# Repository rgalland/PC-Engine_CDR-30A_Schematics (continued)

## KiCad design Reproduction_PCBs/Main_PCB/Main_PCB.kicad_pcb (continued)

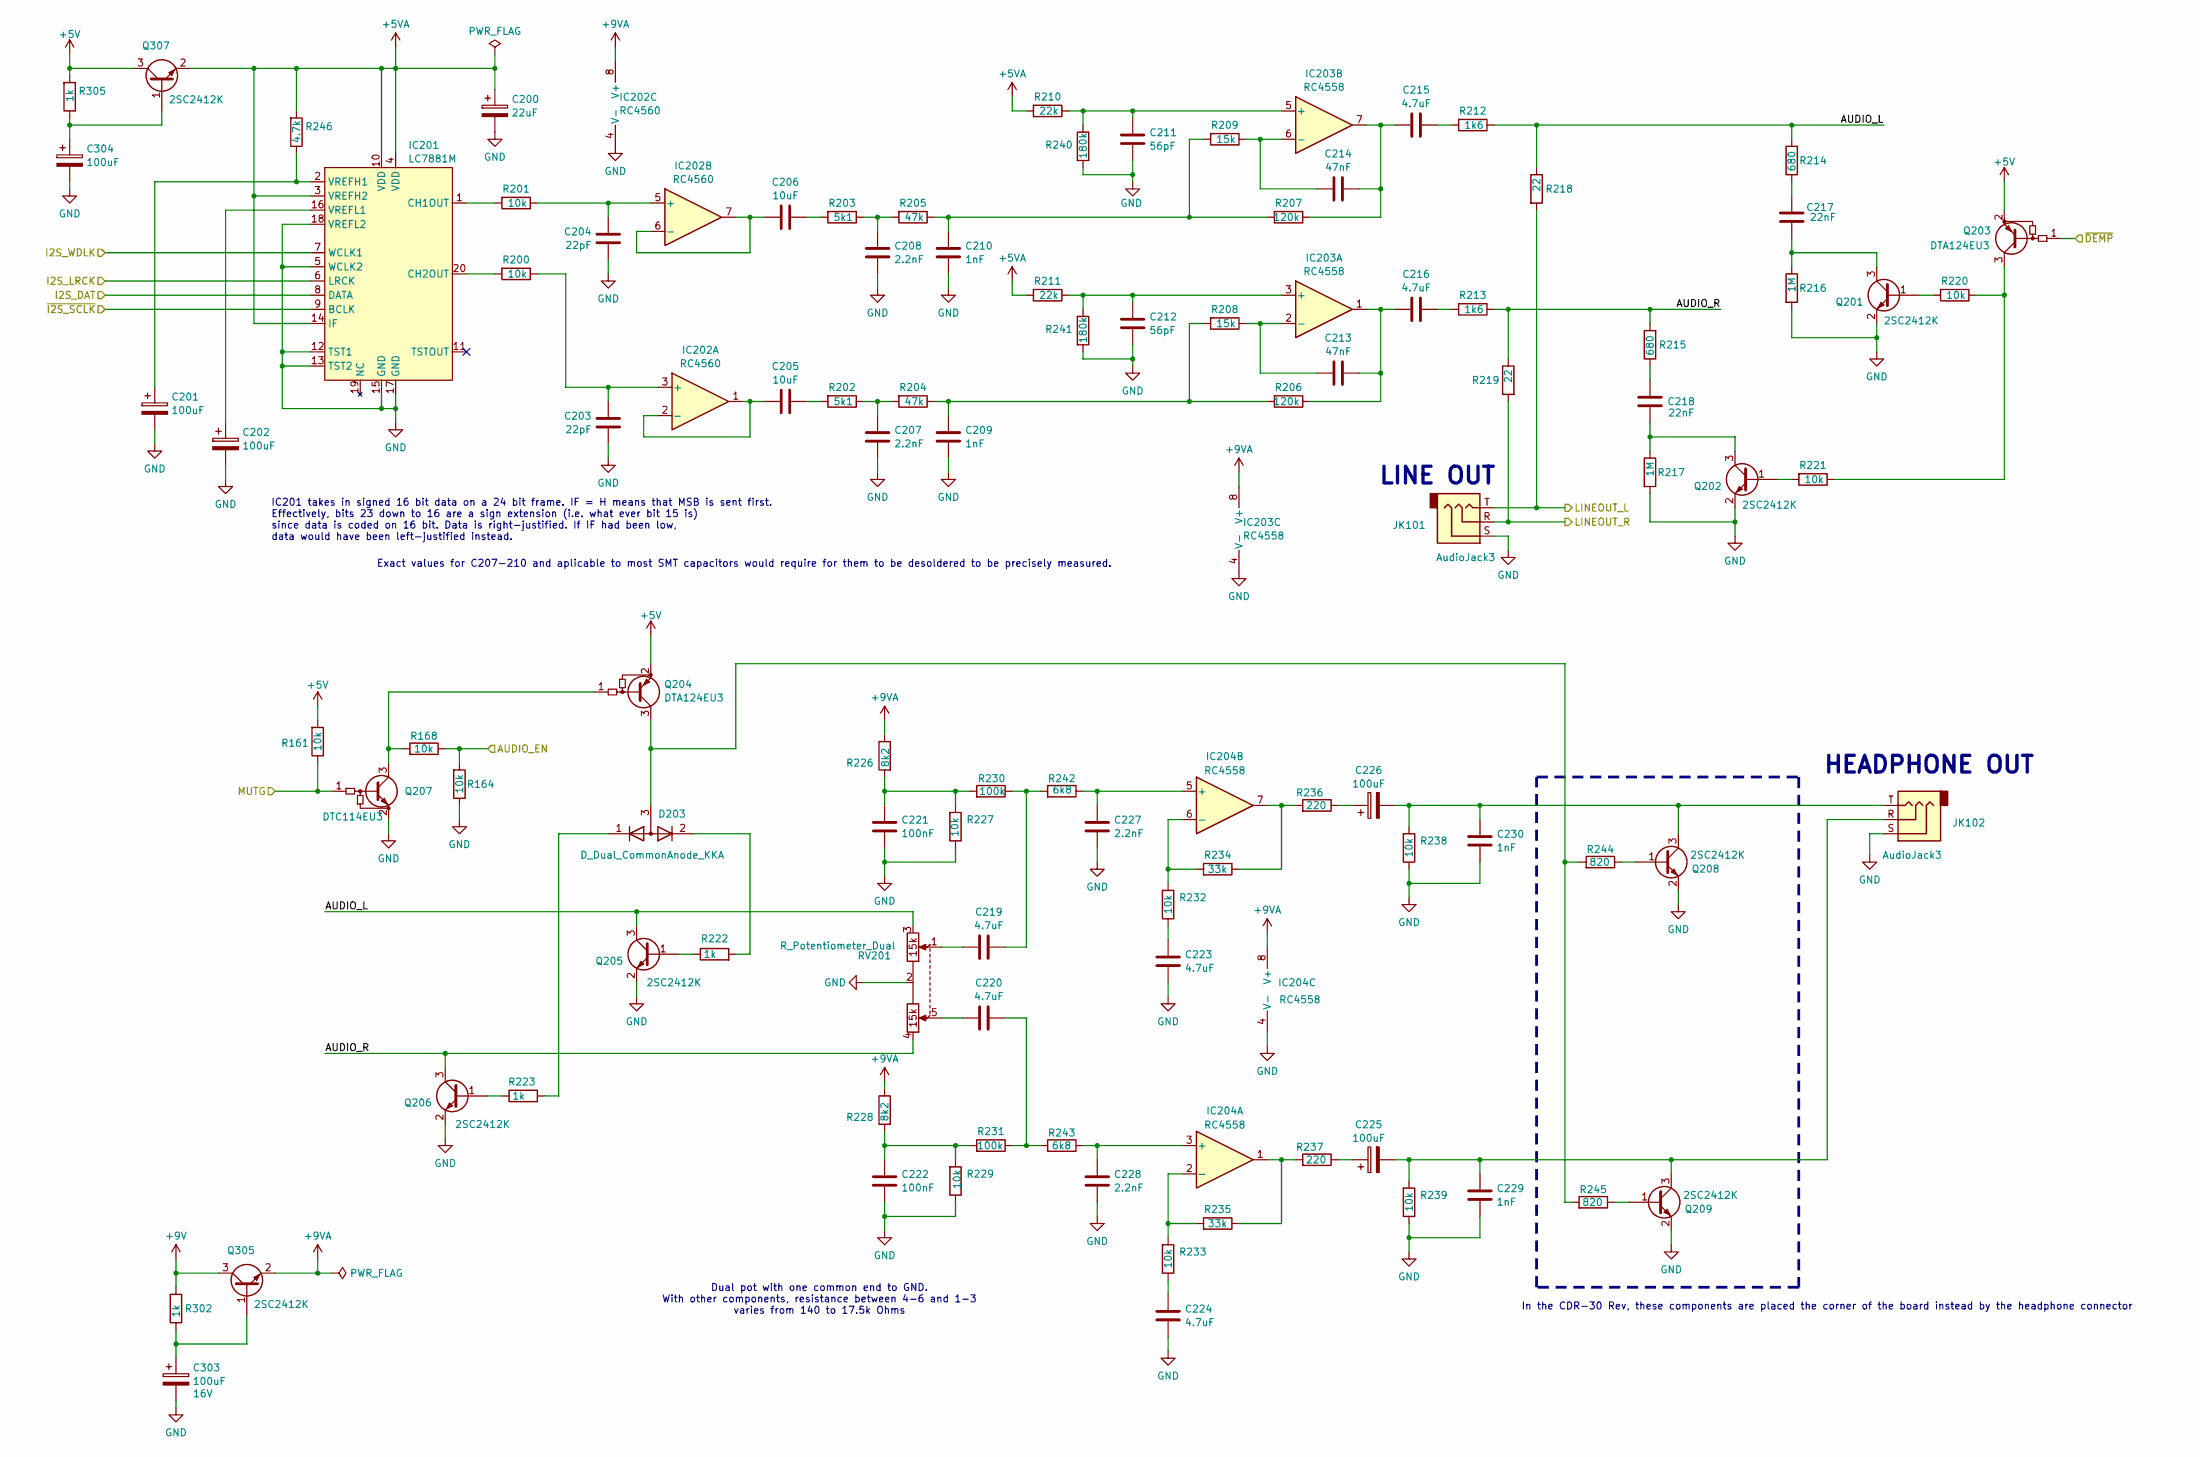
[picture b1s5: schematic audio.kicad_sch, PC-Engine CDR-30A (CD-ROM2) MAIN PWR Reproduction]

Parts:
C200: 22uF; CP_Elec_4x5.4
C201, C202, C225, C226, C304: 100uF; CP_Elec_5x5.4
C203, C204: 22pF; C_0603_1608Metric
C205, C206: 10uF; C_1206_3216Metric
C207, C208, C227, C228: 2.2nF; C_0603_1608Metric
C209, C210, C229, C230: 1nF; C_0603_1608Metric
C211, C212: 56pF; C_0603_1608Metric
C213, C214: 47nF; C_0603_1608Metric
C215, C216, C219, C220, C223, C224: 4.7uF; C_0805_2012Metric
C217, C218: 22nF; C_0603_1608Metric
C221, C222: 100nF; C_0603_1608Metric
C303: 100uF; CP_Elec_6.3x5.4; Voltage 16V
D203: D_Dual_CommonAnode_KKA; SOT-23
IC201: LC7881M; SO-20_5.3x12.6mm_P1.27mm
IC202: RC4560; SOIC-8_3.9x4.9mm_P1.27mm
IC203, IC204: RC4558; SOIC-8_3.9x4.9mm_P1.27mm
JK101, JK102: AudioJack3; Jack_3.5mm_Horizontal
Q201, Q202, Q205, Q206, Q208, Q209, Q305, Q307: 2SC2412K; SOT-23
Q203, Q204: DTA124EU3; SOT-23
Q207: DTC114EU3; SOT-23
R161, R164, R168, R200, R201, R220, R221, R227, R229, R232, R233, R238, R239: 10k; R_0603_1608Metric
R202, R203: 5k1; R_0603_1608Metric
R204, R205: 47k; R_0603_1608Metric
R206, R207: 120k; R_0603_1608Metric
R208, R209: 15k; R_0603_1608Metric
R210, R211: 22k; R_0603_1608Metric
R212, R213: 1k6; R_0603_1608Metric
R214, R215: 680; R_0603_1608Metric
R216, R217: 1M; R_0603_1608Metric
R218, R219: 22; R_0603_1608Metric
R222, R223, R302, R305: 1k; R_0603_1608Metric
R226, R228: 8k2; R_0603_1608Metric
R230, R231: 100k; R_0603_1608Metric
R234, R235: 33k; R_0603_1608Metric
R236, R237: 220; R_0603_1608Metric
R240, R241: 180k; R_0603_1608Metric
R242, R243: 6k8; R_0603_1608Metric
R244, R245: 820; R_0603_1608Metric
R246: 4.7k; R_0603_1608Metric
RV201: R_Potentiometer_Dual; Potentiometer_Double_Horizontal_Common

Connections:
+5V: Q203.2 (E), Q204.2 (E), Q307.3 (C), R161.2, R305.2; also elsewhere on the board
+5VA: C200.1, IC201.3 (VREFH2), IC201.4 (VDD), IC201.10 (VDD), IC201.14 (IF), Q307.2 (E), R210.2, R211.2, R246.2
+9V: Q305.3 (C), R302.2; also elsewhere on the board
+9VA: IC202.8 (V+), IC203.8 (V+), IC204.8 (V+), Q305.2 (E), R226.1, R228.1
/AUDIO/AUDIO_L: Q205.3 (C), R212.1, R214.2, R218.1, RV201.3
/AUDIO/AUDIO_R: Q206.3 (C), R213.1, R215.2, R219.1, RV201.4
/AUDIO/LINEOUT_L: JK101.T, R218.2; also elsewhere on the board
/AUDIO/LINEOUT_R: JK101.R, R219.2; also elsewhere on the board
/AUDIO_EN: R164.2, R168.1; also elsewhere on the board
/I2S_DAT: IC201.8 (DATA); also elsewhere on the board
/I2S_LRCK: IC201.6 (LRCK); also elsewhere on the board
/I2S_WDLK: IC201.7 (WCLK1); also elsewhere on the board
/MUTG: Q207.1 (B), R161.1; also elsewhere on the board
/~DEMP: Q203.1 (B); also elsewhere on the board
/~I2S_SCLK: IC201.9 (BCLK); also elsewhere on the board
GND: C200.2, C201.2, C202.2, C203.1, C204.1, C207.1, C208.1, C209.1, C210.1, C211.1, C212.1, C221.2, C222.2, C223.2, C224.2, C227.2, C228.2, C229.2, C230.2, C303.2, C304.2, IC201.5 (WCLK2), IC201.12 (TST1), IC201.13 (TST2), IC201.15 (GND), IC201.17 (GND), IC201.18 (VREFL2), IC202.4 (V-), IC203.4 (V-), IC204.4 (V-), JK101.S, JK102.S, Q201.2 (E), Q202.2 (E), Q205.2 (E), Q206.2 (E), Q207.2 (E), Q208.2 (E), Q209.2 (E), R164.1, R216.2, R217.2, R227.1, R229.1, R238.1, R239.1, R240.2, R241.2, RV201.2; also elsewhere on the board
unnamed: C205.1, R202.2
unnamed: C206.1, R203.2
unnamed: C207.2, R202.1, R204.2
unnamed: C208.2, R203.1, R205.2
unnamed: C209.2, R204.1, R206.2, R208.2
unnamed: C210.2, R205.1, R207.2, R209.2
unnamed: C213.1, C216.1, IC203.1, R206.1
unnamed: C214.1, C215.1, IC203.7, R207.1
unnamed: C215.2, R212.2
unnamed: C216.2, R213.2
unnamed: C217.2, R214.1
unnamed: C218.2, R215.1
unnamed: C219.1, R230.1, R242.2
unnamed: C219.2, RV201.1
unnamed: C220.1, R231.1, R243.2
unnamed: C220.2, RV201.5
unnamed: C221.1, R226.2, R227.2, R230.2
unnamed: C222.1, R228.2, R229.2, R231.2
unnamed: C223.1, R232.1
unnamed: C224.1, R233.1
unnamed: C225.1, R237.1
unnamed: C226.1, R236.1
unnamed: D203.3 (A), Q204.3 (C), R244.2, R245.2
unnamed: D203.1 (K), R223.2
unnamed: D203.2 (K), R222.2
unnamed: IC201.1 (CH1OUT), R201.2
unnamed: IC201.20 (CH2OUT), R200.2
unnamed: C201.1, IC201.2 (VREFH1), R246.1
unnamed: C202.1, IC201.16 (VREFL1)
unnamed: C203.2, IC202.3 (+), R200.1
unnamed: C205.2, IC202.1, IC202.2 (-)
unnamed: C204.2, IC202.5 (+), R201.1
unnamed: C206.2, IC202.6 (-), IC202.7
unnamed: C212.2, IC203.3 (+), R211.1, R241.1
unnamed: C213.2, IC203.2 (-), R208.1
unnamed: C211.2, IC203.5 (+), R210.1, R240.1
unnamed: C214.2, IC203.6 (-), R209.1
unnamed: IC204.1, R235.1, R237.2
unnamed: IC204.7, R234.1, R236.2
unnamed: C228.1, IC204.3 (+), R243.1
unnamed: IC204.2 (-), R233.2, R235.2
unnamed: C227.1, IC204.5 (+), R242.1
unnamed: IC204.6 (-), R232.2, R234.2
unnamed: Q201.1 (B), R220.2
unnamed: C217.1, Q201.3 (C), R216.1
unnamed: Q202.1 (B), R221.2
unnamed: C218.1, Q202.3 (C), R217.1
unnamed: Q203.3 (C), R220.1, R221.1
unnamed: Q204.1 (B), Q207.3 (C), R168.2
unnamed: Q205.1 (B), R222.1
unnamed: Q206.1 (B), R223.1
unnamed: Q208.1 (B), R244.1
unnamed: C226.2, C230.1, JK102.T, Q208.3 (C), R238.2
unnamed: Q209.1 (B), R245.1
unnamed: C225.2, C229.1, JK102.R, Q209.3 (C), R239.2
unnamed: C303.1, Q305.1 (B), R302.1
unnamed: C304.1, Q307.1 (B), R305.1

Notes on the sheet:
In the CDR-30 Rev, these components are placed the corner of the board instead by the headphone connector
IC201 takes in signed 16 bit data on a 24 bit frame. IF = H means that MSB is sent first. Effectively, bits 23 down to 16 are a sign extension (i.e. what ever bit 15 is) since data is coded on 16 bit. Data is right-justified. If IF had been low, data would have been left-justified instead.
LINE OUT
HEADPHONE OUT
Exact values for C207-210 and aplicable to most SMT capacitors would require for them to be desoldered to be precisely measured.
Dual pot with one common end to GND. With other components, resistance between 4-6 and 1-3 varies from 140 to 17.5k Ohms

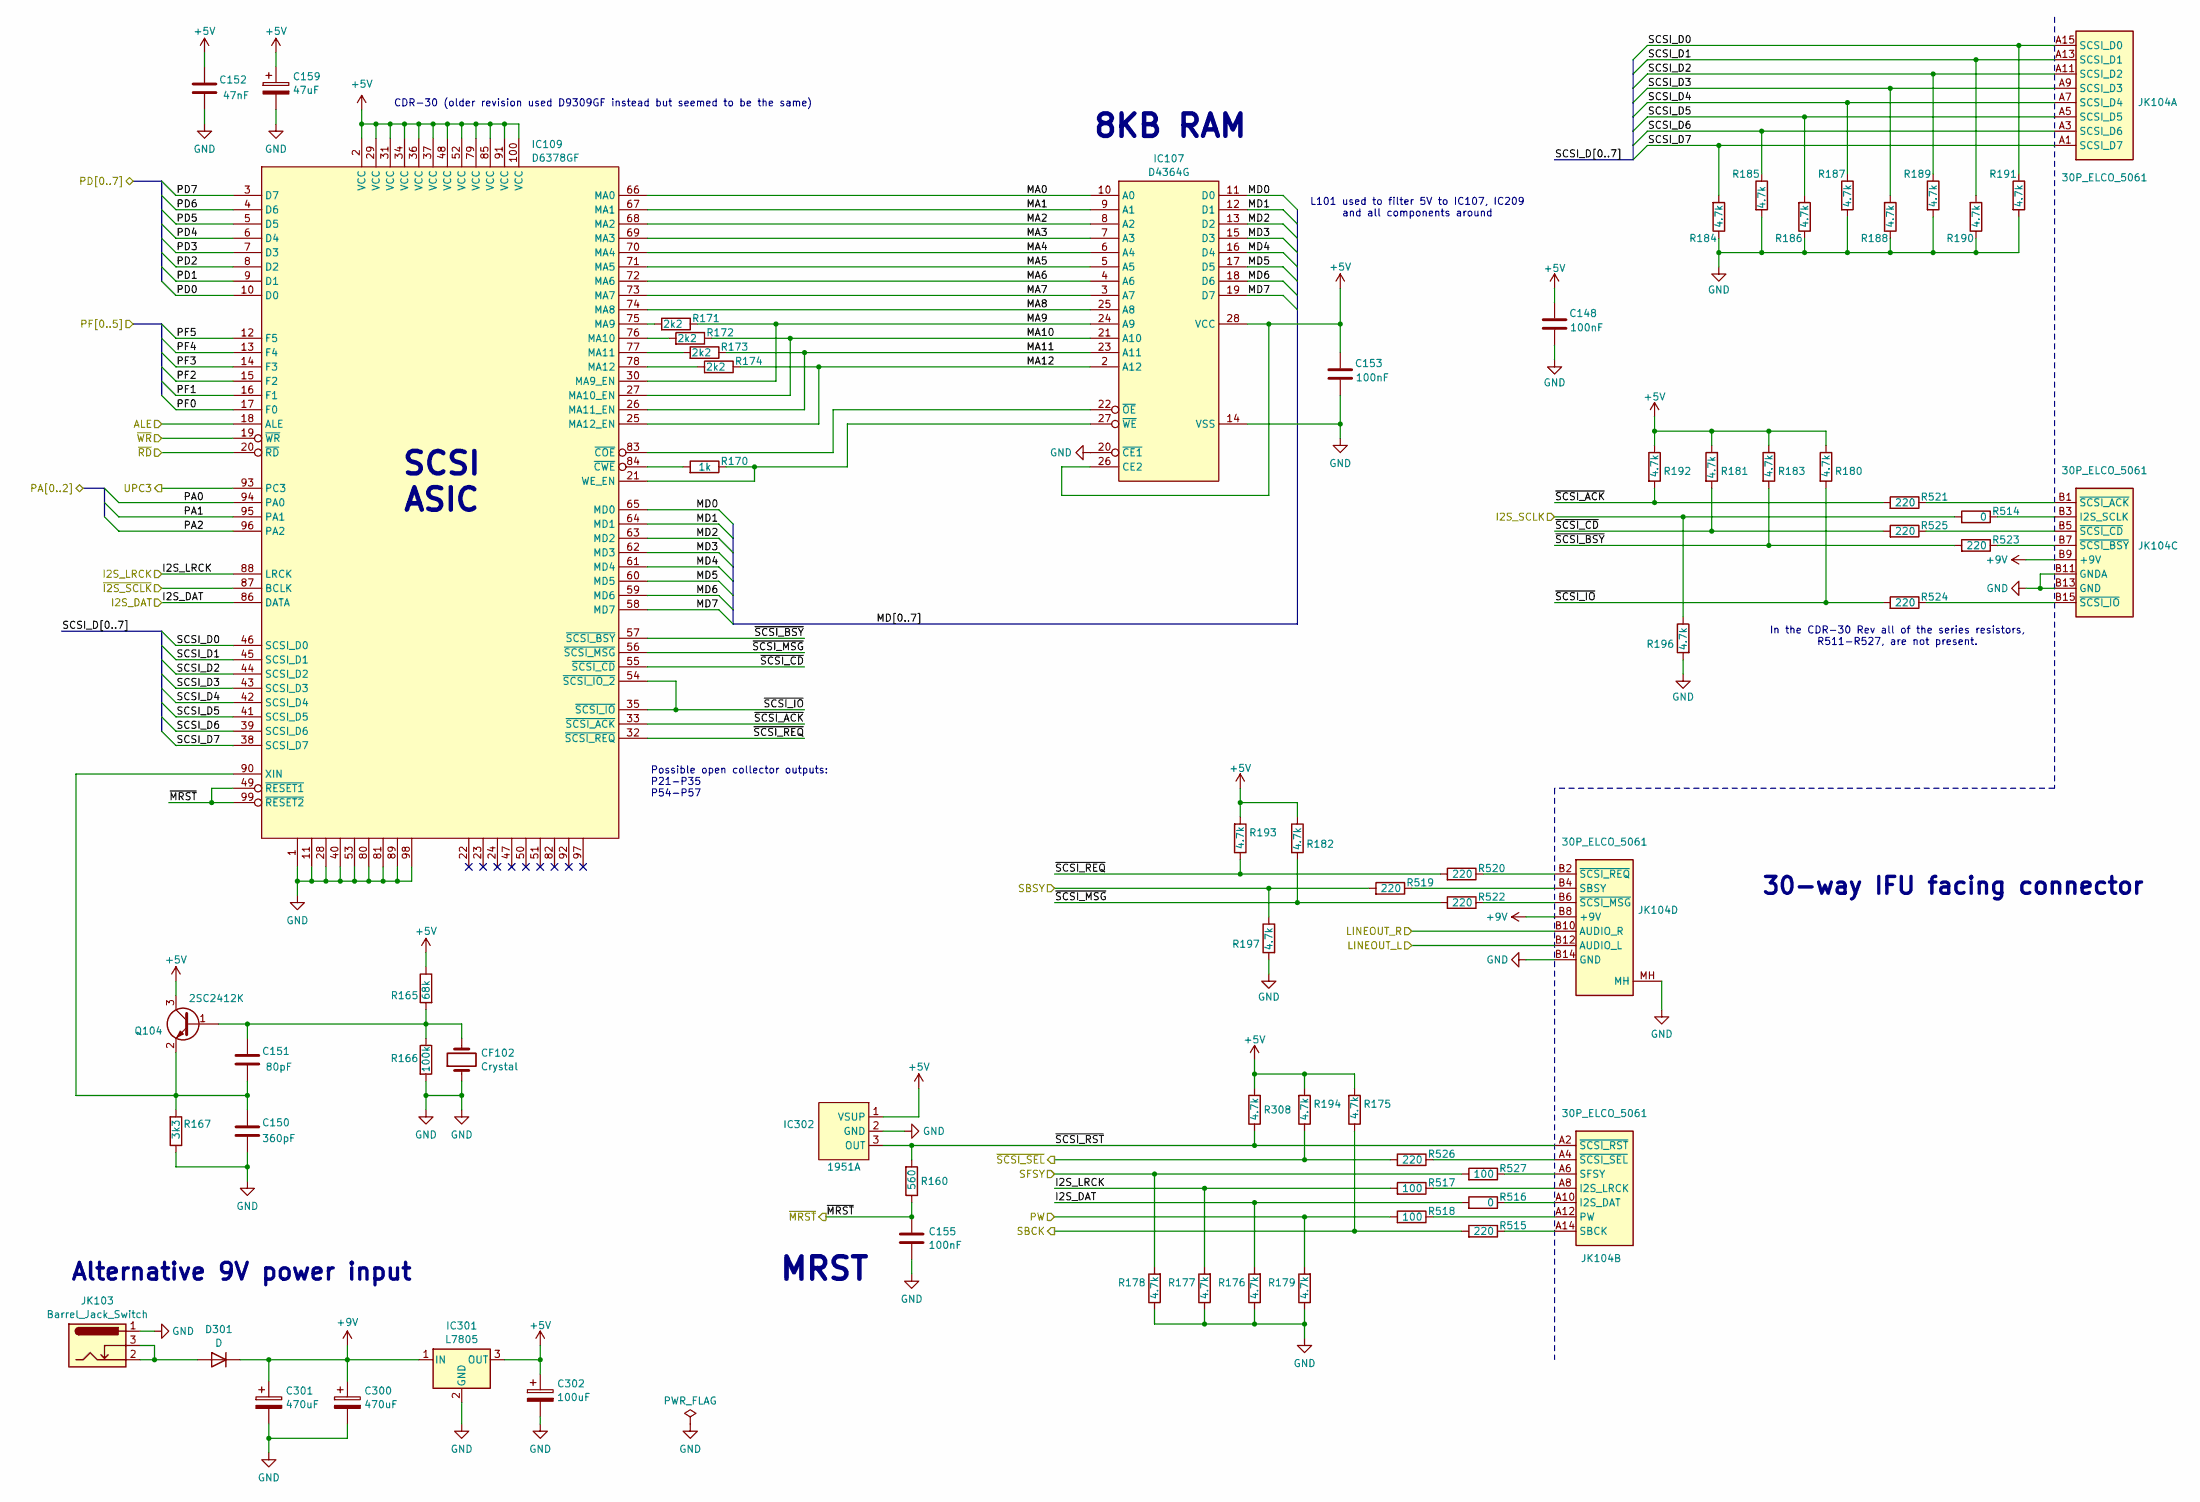
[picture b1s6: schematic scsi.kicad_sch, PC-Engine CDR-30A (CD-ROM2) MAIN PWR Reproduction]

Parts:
C148, C153, C155: 100nF; C_0603_1608Metric
C150: 360pF; C_0603_1608Metric
C151: 80pF; C_0603_1608Metric
C152: 47nF; C_0603_1608Metric
C159: 47uF; CP_Elec_5x5.4
C300, C301: 470uF; CP_Elec_8x10.5
C302: 100uF; CP_Elec_5x5.4
CF102: Crystal; Crystal_HC18-U_Vertical
D301: D; D_A-405_P10.16mm_Horizontal
IC107: D4364G; SOP-28_8.4x18.16mm_P1.27mm
IC109: D6378GF; PQFP-100_14x20mm_P0.65mm
IC301: L7805; TO-220-3_Horizontal_TabDown_HeatSink
IC302: 1951A; SOT-89-3
JK103: Barrel_Jack_Switch; BarrelJack_Horizontal
JK104: 30P_ELCO_5061; TX25-30P-LT-H1E; Manufacturer Part Number 105061030103856+
Q104: 2SC2412K; SOT-23
R160: 560; R_0603_1608Metric
R165: 68k; R_0603_1608Metric
R166: 100k; R_0603_1608Metric
R167: 3k3; R_0603_1608Metric
R170: 1k; R_0603_1608Metric
R171, R172, R173, R174: 2k2; R_0603_1608Metric
R175, R176, R177, R178, R179, R180, R181, R182, R183, R184, R185, R186, R187, R188, R189, R190, R191, R192, R193, R194, R196, R197, R308: 4.7k; R_0603_1608Metric
R514, R516: 0; R_0603_1608Metric
R515, R519, R520, R521, R522, R523, R524, R525, R526: 220; R_0603_1608Metric
R517, R518, R527: 100; R_0603_1608Metric

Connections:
+5V: C148.1, C152.2, C153.1, C159.1, C302.1, IC107.26 (CE2), IC107.28 (VCC), IC109.2 (VCC), IC109.29 (VCC), IC109.31 (VCC), IC109.34 (VCC), IC109.36 (VCC), IC109.37 (VCC), IC109.48 (VCC), IC109.52 (VCC), IC109.79 (VCC), IC109.85 (VCC), IC109.91 (VCC), IC109.100 (VCC), IC301.3 (OUT), IC302.1 (VSUP), Q104.3 (C), R165.1, R175.2, R180.1, R181.1, R182.1, R183.1, R192.1, R193.2, R194.2, R308.2; also elsewhere on the board
+9V: C300.1, C301.1, D301.1 (K), IC301.1 (IN), JK104.B8 (+9V), JK104.B9 (+9V); also elsewhere on the board
/ALE: IC109.18 (ALE); also elsewhere on the board
/AUDIO/LINEOUT_L: JK104.B12 (AUDIO_L); also elsewhere on the board
/AUDIO/LINEOUT_R: JK104.B10 (AUDIO_R); also elsewhere on the board
/I2S_DAT: IC109.86 (DATA), R176.2, R516.2; also elsewhere on the board
/I2S_LRCK: IC109.88 (LRCK), R177.2, R517.2; also elsewhere on the board
/I2S_SCLK: R196.1, R514.2; also elsewhere on the board
/PA0: IC109.94 (PA0); also elsewhere on the board
/PA1: IC109.95 (PA1); also elsewhere on the board
/PA2: IC109.96 (PA2); also elsewhere on the board
/PD0: IC109.10 (D0); also elsewhere on the board
/PD1: IC109.9 (D1); also elsewhere on the board
/PD2: IC109.8 (D2); also elsewhere on the board
/PD3: IC109.7 (D3); also elsewhere on the board
/PD4: IC109.6 (D4); also elsewhere on the board
/PD5: IC109.5 (D5); also elsewhere on the board
/PD6: IC109.4 (D6); also elsewhere on the board
/PD7: IC109.3 (D7); also elsewhere on the board
/PF0: IC109.17 (F0); also elsewhere on the board
/PF1: IC109.16 (F1); also elsewhere on the board
/PF2: IC109.15 (F2); also elsewhere on the board
/PF3: IC109.14 (F3); also elsewhere on the board
/PF4: IC109.13 (F4); also elsewhere on the board
/PF5: IC109.12 (F5); also elsewhere on the board
/PW: R179.2, R518.2; also elsewhere on the board
/SBCK: R175.1, R515.2; also elsewhere on the board
/SBSY: R197.1, R519.2; also elsewhere on the board
/SCSI/MA0: IC107.10 (A0), IC109.66 (MA0)
/SCSI/MA1: IC107.9 (A1), IC109.67 (MA1)
/SCSI/MA2: IC107.8 (A2), IC109.68 (MA2)
/SCSI/MA3: IC107.7 (A3), IC109.69 (MA3)
/SCSI/MA4: IC107.6 (A4), IC109.70 (MA4)
/SCSI/MA5: IC107.5 (A5), IC109.71 (MA5)
/SCSI/MA6: IC107.4 (A6), IC109.72 (MA6)
/SCSI/MA7: IC107.3 (A7), IC109.73 (MA7)
/SCSI/MA8: IC107.25 (A8), IC109.74 (MA8)
/SCSI/MA9: IC107.24 (A9), IC109.30 (MA9_EN), R171.1
/SCSI/MA10: IC107.21 (A10), IC109.27 (MA10_EN), R172.1
/SCSI/MA11: IC107.23 (A11), IC109.26 (MA11_EN), R173.1
/SCSI/MA12: IC107.2 (A12), IC109.25 (MA12_EN), R174.1
/SCSI/MD0: IC107.11 (D0), IC109.65 (MD0)
/SCSI/MD1: IC107.12 (D1), IC109.64 (MD1)
/SCSI/MD2: IC107.13 (D2), IC109.63 (MD2)
/SCSI/MD3: IC107.15 (D3), IC109.62 (MD3)
/SCSI/MD4: IC107.16 (D4), IC109.61 (MD4)
/SCSI/MD5: IC107.17 (D5), IC109.60 (MD5)
/SCSI/MD6: IC107.18 (D6), IC109.59 (MD6)
/SCSI/MD7: IC107.19 (D7), IC109.58 (MD7)
/SCSI/SCSI_D0: IC109.46 (SCSI_D0), JK104.A15 (SCSI_D0), R191.1
/SCSI/SCSI_D1: IC109.45 (SCSI_D1), JK104.A13 (SCSI_D1), R190.2
/SCSI/SCSI_D2: IC109.44 (SCSI_D2), JK104.A11 (SCSI_D2), R189.1
/SCSI/SCSI_D3: IC109.43 (SCSI_D3), JK104.A9 (SCSI_D3), R188.2
/SCSI/SCSI_D4: IC109.42 (SCSI_D4), JK104.A7 (SCSI_D4), R187.1
/SCSI/SCSI_D5: IC109.41 (SCSI_D5), JK104.A5 (SCSI_D5), R186.2
/SCSI/SCSI_D6: IC109.39 (SCSI_D6), JK104.A3 (SCSI_D6), R185.1
/SCSI/SCSI_D7: IC109.38 (SCSI_D7), JK104.A1 (SCSI_D7), R184.2
/SCSI/~SCSI_ACK: IC109.33 (~SCSI_ACK), R192.2, R521.2
/SCSI/~SCSI_BSY: IC109.57 (~SCSI_BSY), R183.2, R523.2
/SCSI/~SCSI_CD: IC109.55 (~SCSI_CD), R181.2, R525.2
/SCSI/~SCSI_IO: IC109.35 (~SCSI_IO), IC109.54 (~SCSI_IO_2), R180.2, R524.2
/SCSI/~SCSI_MSG: IC109.56 (~SCSI_MSG), R182.2, R522.2
/SCSI/~SCSI_REQ: IC109.32 (~SCSI_REQ), R193.1, R520.2
/SCSI/~SCSI_RST: IC302.3 (OUT), JK104.A2 (~SCSI_RST), R160.2, R308.1
/SFSY: R178.2, R527.2; also elsewhere on the board
/UPC3: IC109.93 (PC3); also elsewhere on the board
/~I2S_SCLK: IC109.87 (BCLK); also elsewhere on the board
/~MRST: C155.1, IC109.49 (~RESET1), IC109.99 (~RESET2), R160.1; also elsewhere on the board
/~RD: IC109.20 (~RD); also elsewhere on the board
/~SCSI_SEL: R194.1, R526.2; also elsewhere on the board
/~WR: IC109.19 (~WR); also elsewhere on the board
GND: C148.2, C150.1, C152.1, C153.2, C155.2, C159.2, C300.2, C301.2, C302.2, CF102.1, IC107.14 (VSS), IC107.20 (~CE1), IC109.1, IC109.11, IC109.28, IC109.40, IC109.53, IC109.80, IC109.81, IC109.89, IC109.98, IC301.2 (GND), IC302.2 (GND), JK103.1, JK104.B11 (GNDA), JK104.B13 (GND), JK104.B14 (GND), JK104.MH, R166.2, R167.1, R176.1, R177.1, R178.1, R179.1, R184.1, R185.2, R186.1, R187.2, R188.1, R189.2, R190.1, R191.2, R196.2, R197.2; also elsewhere on the board
unnamed: D301.2 (A), JK103.2, JK103.3
unnamed: IC107.22 (~OE), IC109.83 (~COE)
unnamed: IC107.27 (~WE), IC109.21 (WE_EN), R170.1
unnamed: IC109.75 (MA9), R171.2
unnamed: IC109.76 (MA10), R172.2
unnamed: IC109.77 (MA11), R173.2
unnamed: IC109.78 (MA12), R174.2
unnamed: C150.2, C151.1, IC109.90 (XIN), Q104.2 (E), R167.2
unnamed: IC109.84 (~CWE), R170.2
unnamed: JK104.A10 (I2S_DAT), R516.1
unnamed: JK104.A8 (I2S_LRCK), R517.1
unnamed: JK104.A12 (PW), R518.1
unnamed: JK104.A14 (SBCK), R515.1
unnamed: JK104.A6 (SFSY), R527.1
unnamed: JK104.A4 (~SCSI_SEL), R526.1
unnamed: JK104.B3 (I2S_SCLK), R514.1
unnamed: JK104.B1 (~SCSI_ACK), R521.1
unnamed: JK104.B7 (~SCSI_BSY), R523.1
unnamed: JK104.B5 (~SCSI_CD), R525.1
unnamed: JK104.B15 (~SCSI_IO), R524.1
unnamed: JK104.B4 (SBSY), R519.1
unnamed: JK104.B6 (~SCSI_MSG), R522.1
unnamed: JK104.B2 (~SCSI_REQ), R520.1
unnamed: C151.2, CF102.2, Q104.1 (B), R165.2, R166.1

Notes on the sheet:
MRST
30-way IFU facing connector
L101 used to filter 5V to IC107, IC209 and all components around
8KB RAM
Possible open collector outputs: P21-P35 P54-P57
SCSI ASIC
In the CDR-30 Rev all of the series resistors, R511-R527, are not present.
Alternative 9V power input
CDR-30 (older revision used D9309GF instead but seemed to be the same)

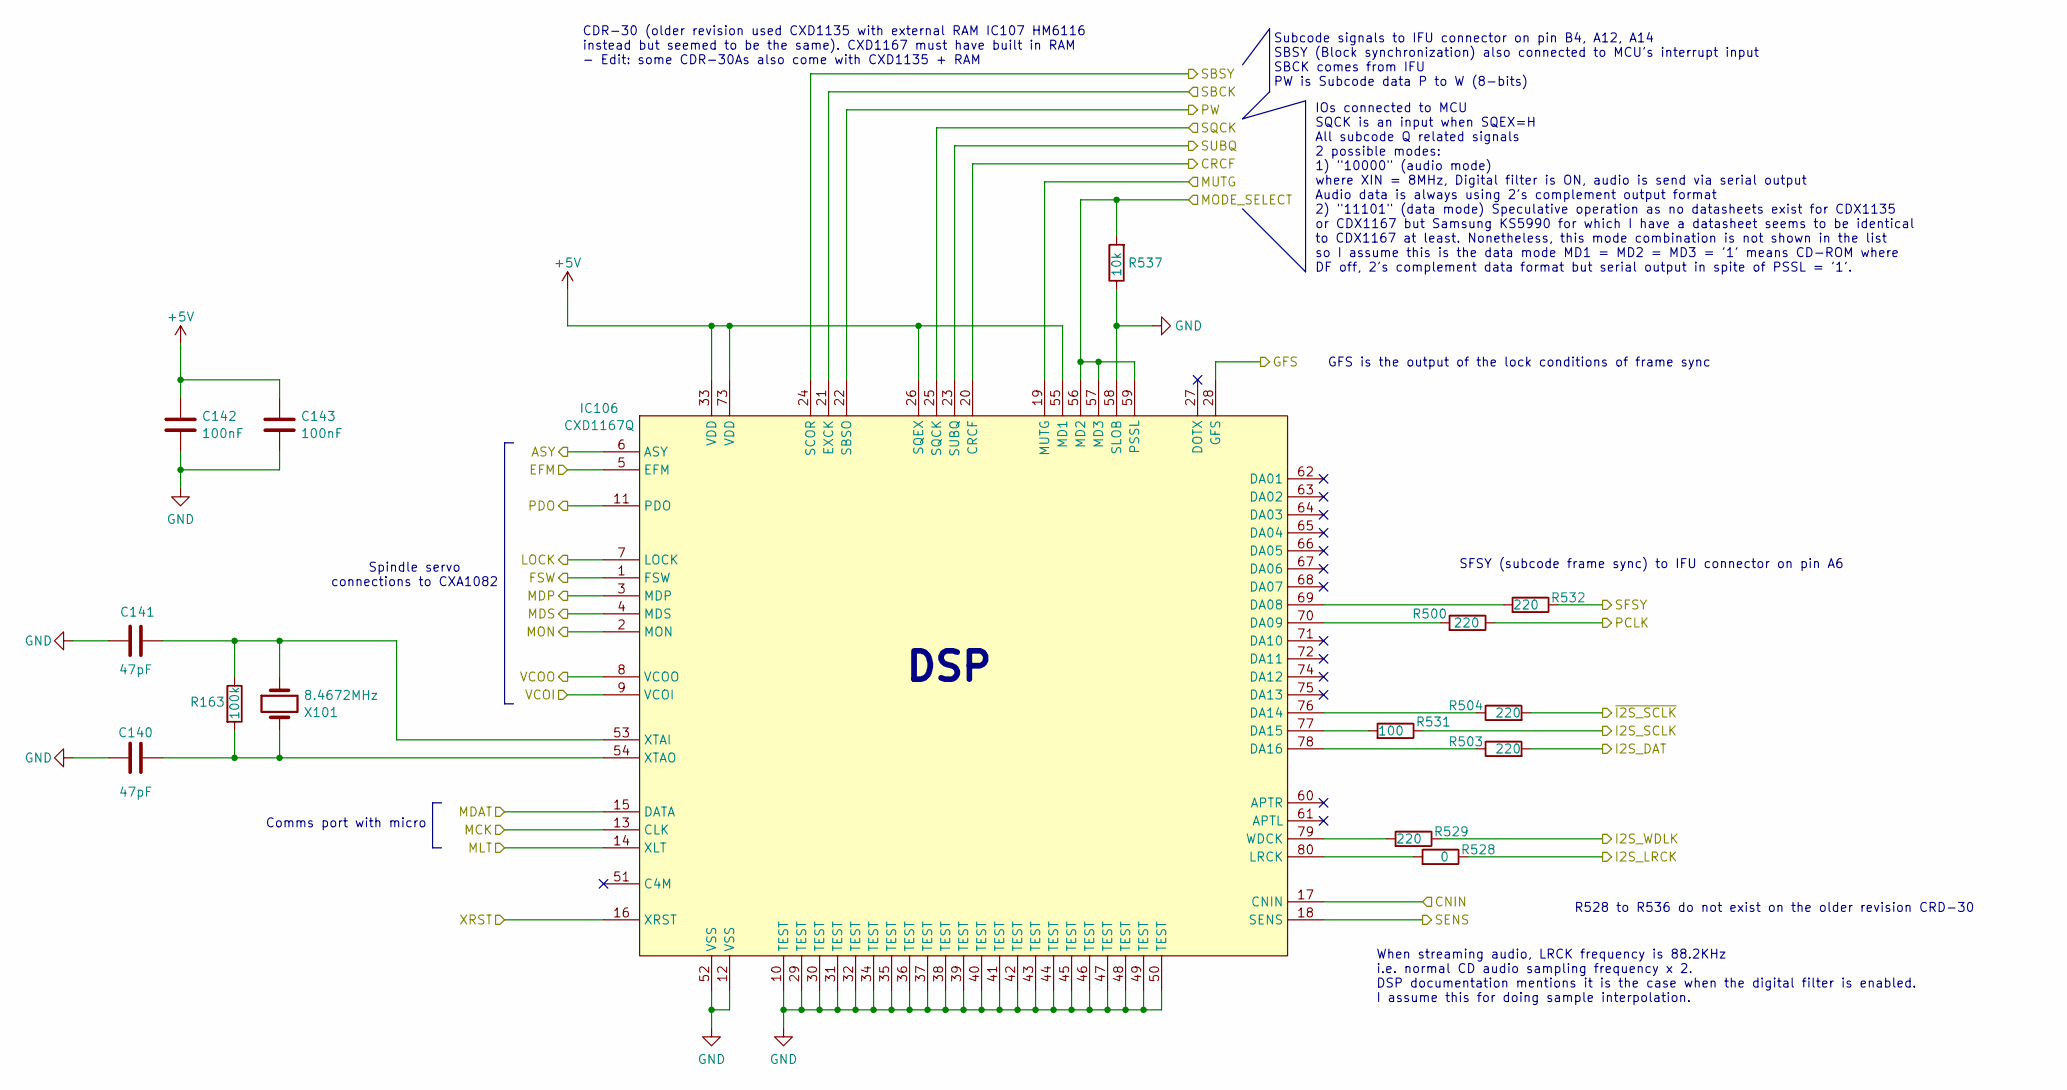
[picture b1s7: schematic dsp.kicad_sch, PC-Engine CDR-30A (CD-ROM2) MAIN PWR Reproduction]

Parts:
C140, C141: 47pF; C_0603_1608Metric
C142, C143: 100nF; C_0603_1608Metric
IC106: CXD1167Q; PQFP-80_14x20mm_P0.8mm
R163: 100k; R_0603_1608Metric
R500, R503, R504, R529, R532: 220; R_0603_1608Metric
R528: 0; R_0603_1608Metric
R531: 100; R_0603_1608Metric
R537: 10k; R_0603_1608Metric
X101: 8.4672MHz; Crystal_HC18-U_Horizontal

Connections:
+5V: C142.1, C143.1, IC106.26 (SQEX), IC106.33 (VDD), IC106.55 (MD1), IC106.73 (VDD); also elsewhere on the board
/CNIN: IC106.17 (CNIN); also elsewhere on the board
/CRCF: IC106.20 (CRCF); also elsewhere on the board
/DSP/ASY: IC106.6 (ASY); also elsewhere on the board
/DSP/EFM: IC106.5 (EFM); also elsewhere on the board
/DSP/PCLK: R500.1; also elsewhere on the board
/FSW: IC106.1 (FSW); also elsewhere on the board
/GFS: IC106.28 (GFS); also elsewhere on the board
/I2S_DAT: R503.2; also elsewhere on the board
/I2S_LRCK: R528.1; also elsewhere on the board
/I2S_SCLK: R531.1; also elsewhere on the board
/I2S_WDLK: R529.1; also elsewhere on the board
/LOCK: IC106.7 (LOCK); also elsewhere on the board
/MCK: IC106.13 (CLK); also elsewhere on the board
/MDAT: IC106.15 (DATA); also elsewhere on the board
/MDP: IC106.3 (MDP); also elsewhere on the board
/MDS: IC106.4 (MDS); also elsewhere on the board
/MLT: IC106.14 (XLT); also elsewhere on the board
/MODE_SELECT: IC106.56 (MD2), IC106.57 (MD3), IC106.59 (PSSL), R537.2; also elsewhere on the board
/MON: IC106.2 (MON); also elsewhere on the board
/MUTG: IC106.19 (MUTG); also elsewhere on the board
/PDO: IC106.11 (PDO); also elsewhere on the board
/PW: IC106.22 (SBSO); also elsewhere on the board
/SBCK: IC106.21 (EXCK); also elsewhere on the board
/SBSY: IC106.24 (SCOR); also elsewhere on the board
/SENS: IC106.18 (SENS); also elsewhere on the board
/SFSY: R532.1; also elsewhere on the board
/SQCK: IC106.25 (SQCK); also elsewhere on the board
/SUBQ: IC106.23 (SUBQ); also elsewhere on the board
/VCOI: IC106.9 (VCOI); also elsewhere on the board
/VCOO: IC106.8 (VCOO); also elsewhere on the board
/XRST: IC106.16 (XRST); also elsewhere on the board
/~I2S_SCLK: R504.2; also elsewhere on the board
GND: C140.1, C141.2, C142.2, C143.2, IC106.10 (TEST), IC106.12 (VSS), IC106.29 (TEST), IC106.30 (TEST), IC106.31 (TEST), IC106.32 (TEST), IC106.34 (TEST), IC106.35 (TEST), IC106.36 (TEST), IC106.37 (TEST), IC106.38 (TEST), IC106.39 (TEST), IC106.40 (TEST), IC106.41 (TEST), IC106.42 (TEST), IC106.43 (TEST), IC106.44 (TEST), IC106.45 (TEST), IC106.46 (TEST), IC106.47 (TEST), IC106.48 (TEST), IC106.49 (TEST), IC106.50 (TEST), IC106.52 (VSS), IC106.58 (SLOB), R537.1; also elsewhere on the board
unnamed: IC106.69 (DA08), R532.2
unnamed: IC106.70 (DA09), R500.2
unnamed: IC106.76 (DA14), R504.1
unnamed: IC106.77 (DA15), R531.2
unnamed: IC106.78 (DA16), R503.1
unnamed: IC106.80 (LRCK), R528.2
unnamed: IC106.79 (WDCK), R529.2
unnamed: C141.1, IC106.53 (XTAI), R163.1, X101.1
unnamed: C140.2, IC106.54 (XTAO), R163.2, X101.2

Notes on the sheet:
DSP
Comms port with micro
When streaming audio, LRCK frequency is 88.2KHz i.e. normal CD audio sampling frequency x 2. DSP documentation mentions it is the case when the digital filter is enabled. I assume this for doing sample interpolation.
GFS is the output of the lock conditions of frame sync
Subcode signals to IFU connector on pin B4, A12, A14 SBSY (Block synchronization) also connected to MCU's interrupt input SBCK comes from IFU PW is Subcode data P to W (8-bits)
R528 to R536 do not exist on the older revision CRD-30
IOs connected to MCU SQCK is an input when SQEX=H All subcode Q related signals 2 possible modes: 1) "10000" (audio mode) where XIN = 8MHz, Digital filter is ON, audio is send via serial output Audio data is always using 2's complement output format 2) "11101" (data mode) Speculative operation as n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
CDR-30 (older revision used CXD1135 with external RAM IC107 HM6116 instead but seemed to be the same). CXD1167 must have built in RAM - Edit: some CDR-30As also come with CXD1135 + RAM
Spindle servo connections to CXA1082
SFSY (subcode frame sync) to IFU connector on pin A6

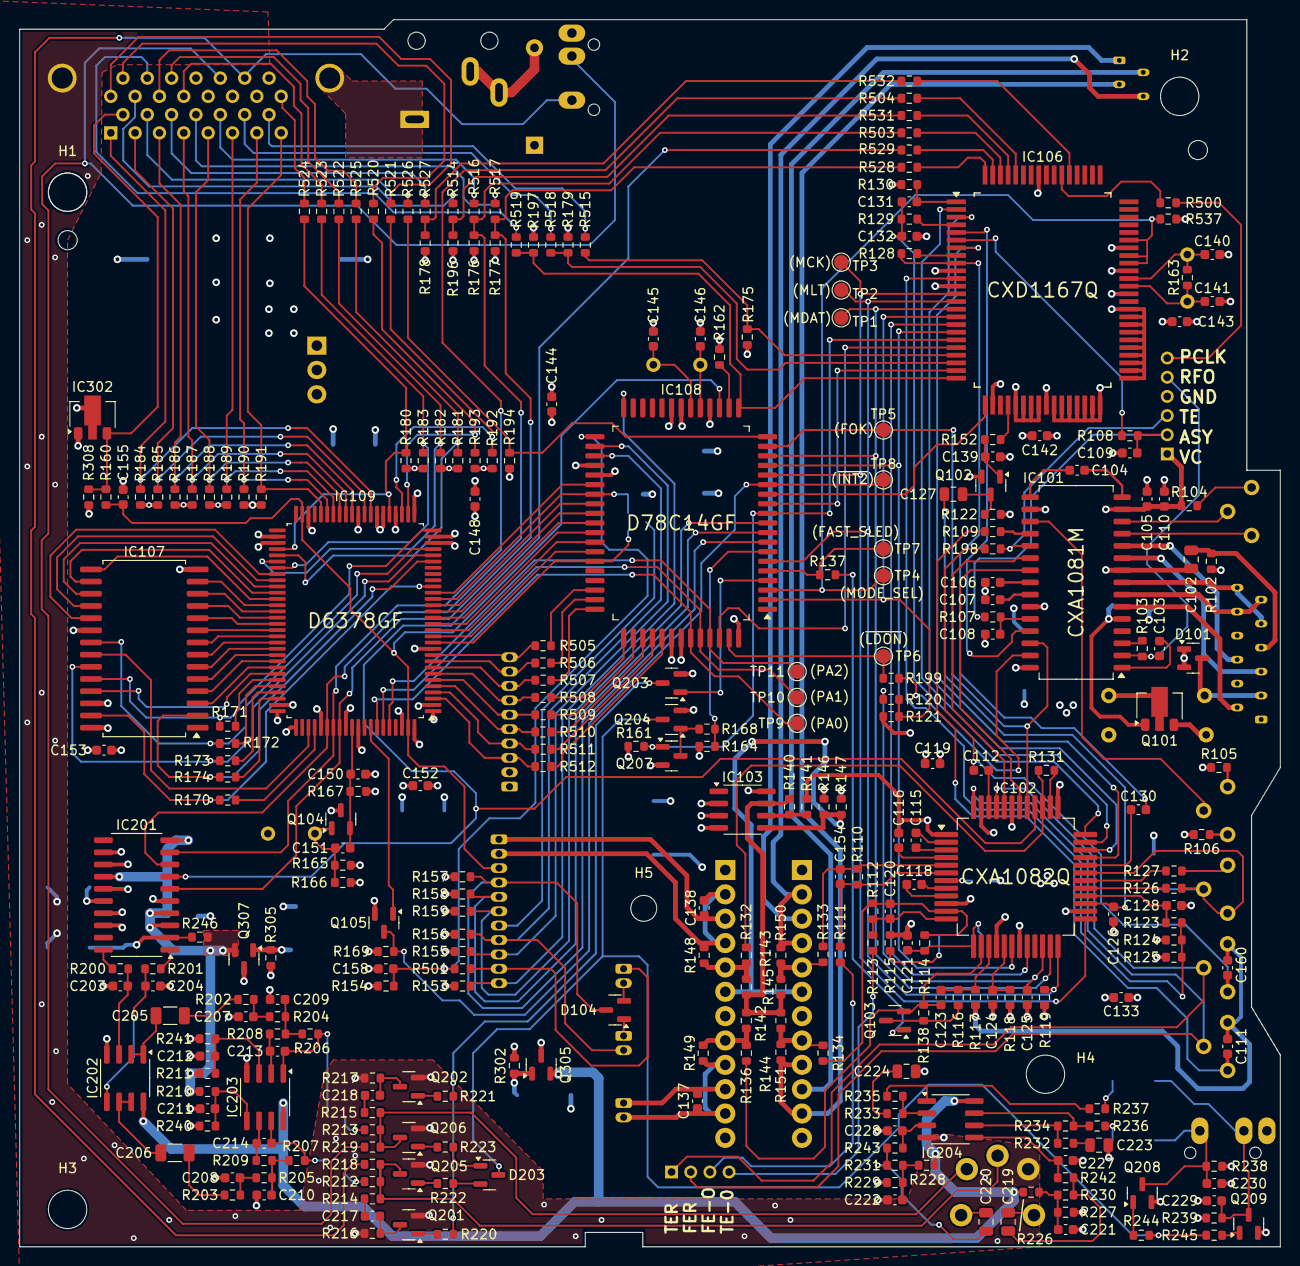
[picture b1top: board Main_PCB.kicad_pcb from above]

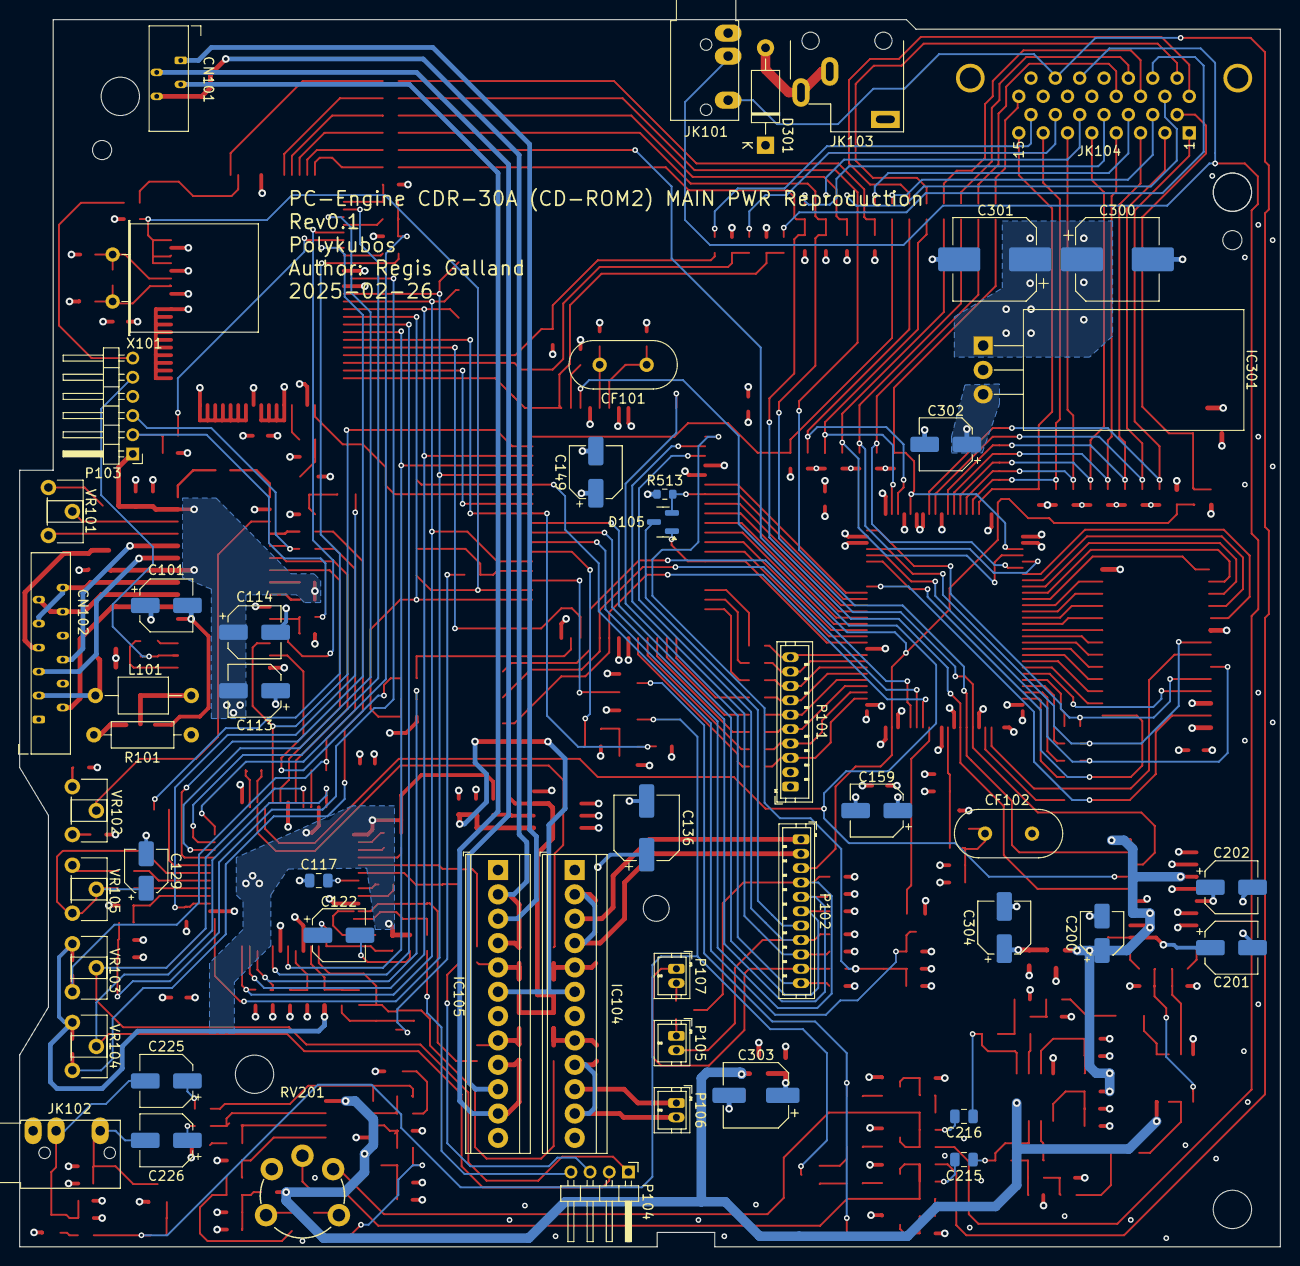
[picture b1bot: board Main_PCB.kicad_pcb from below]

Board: 4 copper layers, 131.5 x 128.0 mm, 342 parts (51 on the bottom side), 301 nets.
